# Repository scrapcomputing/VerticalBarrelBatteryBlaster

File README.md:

# Vertical Barrel Battery Blaster

Vertical Barrel Battery Blaster is a very small PCB for replacing old rechargeable barrel-type CMOS batteries with non-rechargeable CR2032 Lithium batteries.
This particular PCB is for the vertical type of CR2032 battery holders.

Barrel batteries were quite common on vintage computer motherboards up until the 486 era.
These barrel batteries tend to leak, damaging the motherboard and the surrounding components.

<p float="left">

> **Warning**
> Older systems may require a higher voltage than the 3V - diode voltage drop that this board can provide. For these systems please use a board with a MAX40200 ideal diode like [Not-A-Varta](https://github.com/wiretap-retro/Not-A-Varta-CR2032) or [Horizontal Barrel Battery Blaster](https://github.com/scrapcomputing/HorizontalBarrelBatteryBlaster) rev.0.2+.

# Similar Projects
- [Not-A-Varta](https://github.com/wiretap-retro/Not-A-Varta-CR2032) Uses a MAX40200 ideal diode
- [Horizontal Barrel Battery Blaster](https://github.com/scrapcomputing/HorizontalBarrelBatteryBlaster) Works with several types of diodes, including a MAX40200.
- [Barrel Battery Blaster](https://github.com/scrapcomputing/BarrelBatteryBlaster)

# Video
https://www.youtube.com/watch?v=O76bEk7QzwA

# How can I get one?

You can order one at your PCB fab of choice.
The simplest way is to use the zipped gerber files from the [releases](https://github.com/scrapcomputing/VerticalBarrelBatteryBlaster/releases).

# Bill of materials

Item                                           | #   | Description
-----------------------------------------------|-----|-----------------------------------------
Male header pins out of a 2.54mm pitch header  | 2   | For connecting the VerticalBarrelBatteryBlaster to the motherboard
Vertically mounted 3-lead CR2032 battery holder| 1   | For the CR2032 Lithium battery
Diode (preferably schottky, like 1N5817)       | 1   | To prevent the Lithium battery from being charged by the motherboard

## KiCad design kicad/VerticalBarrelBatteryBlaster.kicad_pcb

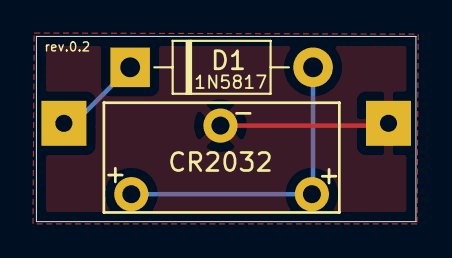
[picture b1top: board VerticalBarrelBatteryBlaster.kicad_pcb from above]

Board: 2 copper layers, 21.1 x 10.3 mm, 3 parts (1 on the bottom side), 3 nets.

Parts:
BarrelBattery1: BarrelBattery; barrel_battery_pins
CR2032: CR2032; cr2032_vertical_battery_holder
D1: 1N5817; D_DO-41_SOD81_P10.16mm_Horizontal

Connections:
GND: BarrelBattery1.2, CR2032.2
VBAT: CR2032.1, D1.2
VDiode: BarrelBattery1.1, D1.1

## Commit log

2023-06-27 Initial commit rev.0.1
2023-07-15 Improve README
2023-07-15 Rev.0.2: Improves printed text
2023-11-06 README: Add links to other project and to video
